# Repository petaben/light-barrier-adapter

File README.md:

# light-barrier-adapter

Adapter circuit for these 5 pin [light barriers](https://omronfs.omron.com/en_US/ecb/products/pdf/en-ee_sx3161_w11_4161_w11.pdf).
To make the interface to the light barrier easier and to avoid having 5 cables going to the controller board I use this simple adapter.

This repository contains the PCB design but it's as well easy to make the adapter on a stripboard.

### PCB

### Stripboard

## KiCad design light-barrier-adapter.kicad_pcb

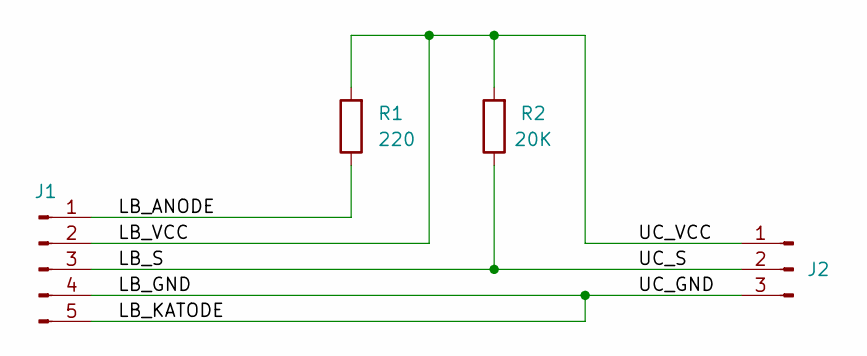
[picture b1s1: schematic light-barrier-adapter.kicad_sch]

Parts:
J1: Conn_PinHeader_1x05_P2.54mm_Vertical_THT_D1mm; PinHeader_1x05_P2.54mm_Vertical_THT_D1mm
J2: Conn_PinHeader_1x03_P2.54mm_Vertical_THT_D1mm; PinHeader_1x03_P2.54mm_Vertical_THT_D1mm
R1: 220; R_Axial_DIN0207_L6.3mm_D2.5mm_P10.16mm_Horizontal
R2: 20K; R_Axial_DIN0207_L6.3mm_D2.5mm_P10.16mm_Horizontal

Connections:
/LB_ANODE: J1.1, R1.1
/LB_GND: J1.4, J1.5, J2.3
/LB_S: J1.3, J2.2, R2.1
/LB_VCC: J1.2, J2.1, R1.2, R2.2

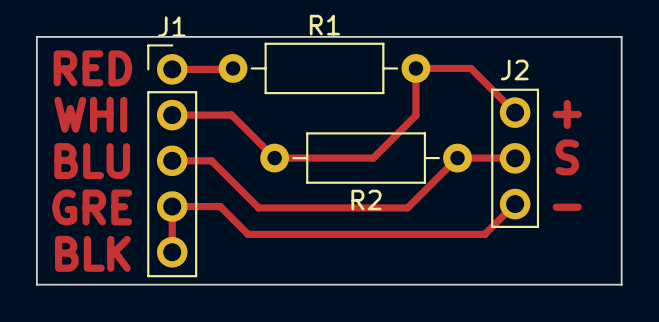
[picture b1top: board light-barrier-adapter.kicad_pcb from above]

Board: 2 copper layers, 32.5 x 13.8 mm, 4 parts (0 on the bottom side), 4 nets.

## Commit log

2022-08-01 feat(): initial board design
    I producted 3 of them
2022-08-01 feat(): make board smaller
2022-08-08 doc(): relative link to pic
2022-08-08 doc(): add pics
2022-08-08 added pictures of adapters
